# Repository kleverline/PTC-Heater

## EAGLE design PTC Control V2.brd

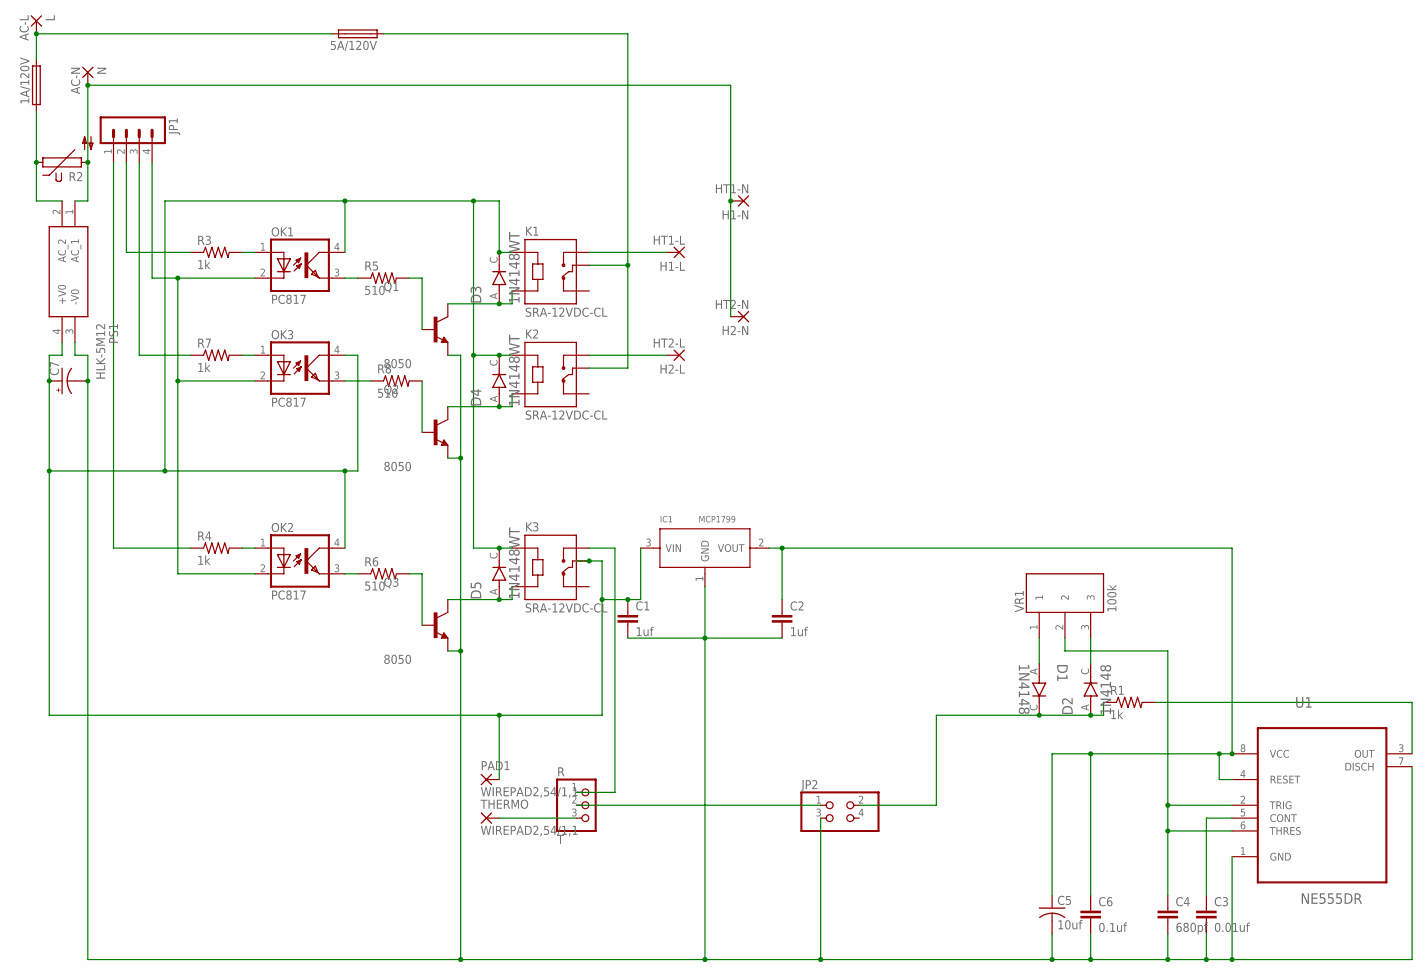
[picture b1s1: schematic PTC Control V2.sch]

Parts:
1A/120V, 5A/120V: SH25
C1, C2: 1uf; C0805
C3: 0.01uf; C0805
C4: 680pf; C0805
C5: 10uf; C1206
C6: 0.1uf; C0805
C7: CPOL-USE3.5-8; E3,5-8
D1, D2: 1N4148; SODFL1608X70N
D3, D4, D5: 1N4148WT; SODFL1608X70N
H1-L: HT1-L; 3,17/1,2
H1-N: HT1-N; 3,17/1,2
H2-L: HT2-L; 3,17/1,2
H2-N: HT2-N; 3,17/1,2
IC1: MCP1799; SOT-23
JP1: MA04-1
JP2: PINHD-2X2; 2X02
K1, K2, K3: SRA-12VDC-CL; RELAY_1-1721150-3
L: AC-L; 3,81/1,4
N: AC-N; 3,81/1,4
OK1, OK2, OK3: PC817; DIL04
PAD1: WIREPAD2,54/1,1; 2,54/1,1
PS1: HLK-5M12; HLK5M12
Q1, Q2, Q3: 8050; TRANS_MMSS8050-H-TP
R: T; 1X03
R1, R3, R4, R7: 1k; R0805
R2: S10K250
R5, R6, R8: 510; R0805
THERMO: WIREPAD2,54/1,1; 2,54/1,1
U1: NE555DR; SOIC127P600X175-8N
VR1: 100k; TRIM_416XA503P

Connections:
GND: C1.2, C2.2, C3.2, C4.2, C5.2, C6.2, C7.-, IC1.1 (GND), JP2.3, PS1.3 (-V0), Q1.2 (E), Q2.2 (E), Q3.2 (E), U1.1 (GND), U1.7 (DISCH)
unnamed: JP2.1, R.2
unnamed: C3.1, U1.5 (CONT)
unnamed: D1.A, VR1.1
unnamed: D2.C, VR1.3
unnamed: 1A/120V.1, PS1.2 (AC_2), R2.1
unnamed: R1.2, U1.3 (OUT)
unnamed: C4.1, U1.2 (TRIG), U1.6 (THRES), VR1.2
unnamed: H1-N.1, H2-N.1, N.1, PS1.1 (AC_1), R2.2
unnamed: OK3.3 (EMIT), R8.1
unnamed: 5A/120V.1, K1.COM, K2.COM
unnamed: OK1.1 (A), R3.2
unnamed: OK2.1 (A), R4.2
unnamed: JP1.4, OK1.2 (C), OK2.2 (C), OK3.2 (C)
unnamed: JP1.1, R4.1
unnamed: JP1.2, R3.1
unnamed: OK1.3 (EMIT), R5.1
unnamed: OK2.3 (EMIT), R6.1
unnamed: Q3.1 (B), R6.2
unnamed: Q2.1 (B), R8.2
unnamed: JP1.3, R7.1
unnamed: D4.A, K2.A2, Q2.3 (C)
unnamed: D5.A, K3.A2, Q3.3 (C)
unnamed: OK3.1 (A), R7.2
unnamed: Q1.1 (B), R5.2
unnamed: H1-L.1, K1.NO
unnamed: D3.A, K1.A2, Q1.3 (C)
unnamed: H2-L.1, K2.NO
unnamed: 1A/120V.2, 5A/120V.2, L.1
unnamed: K3.NO, R.1
unnamed: R.3, THERMO.1
unnamed: C1.1, C7.+, D3.C, D4.C, D5.C, IC1.3 (VIN), K1.A1, K2.A1, K3.A1, K3.COM, OK1.4 (COL), OK2.4 (COL), OK3.4 (COL), PAD1.1, PS1.4 (+V0)
PWM-SIG: D1.C, D2.A, JP2.2, R1.1
VCC-5V: C2.1, C5.1, C6.1, IC1.2 (VOUT), U1.4 (RESET), U1.8 (VCC)

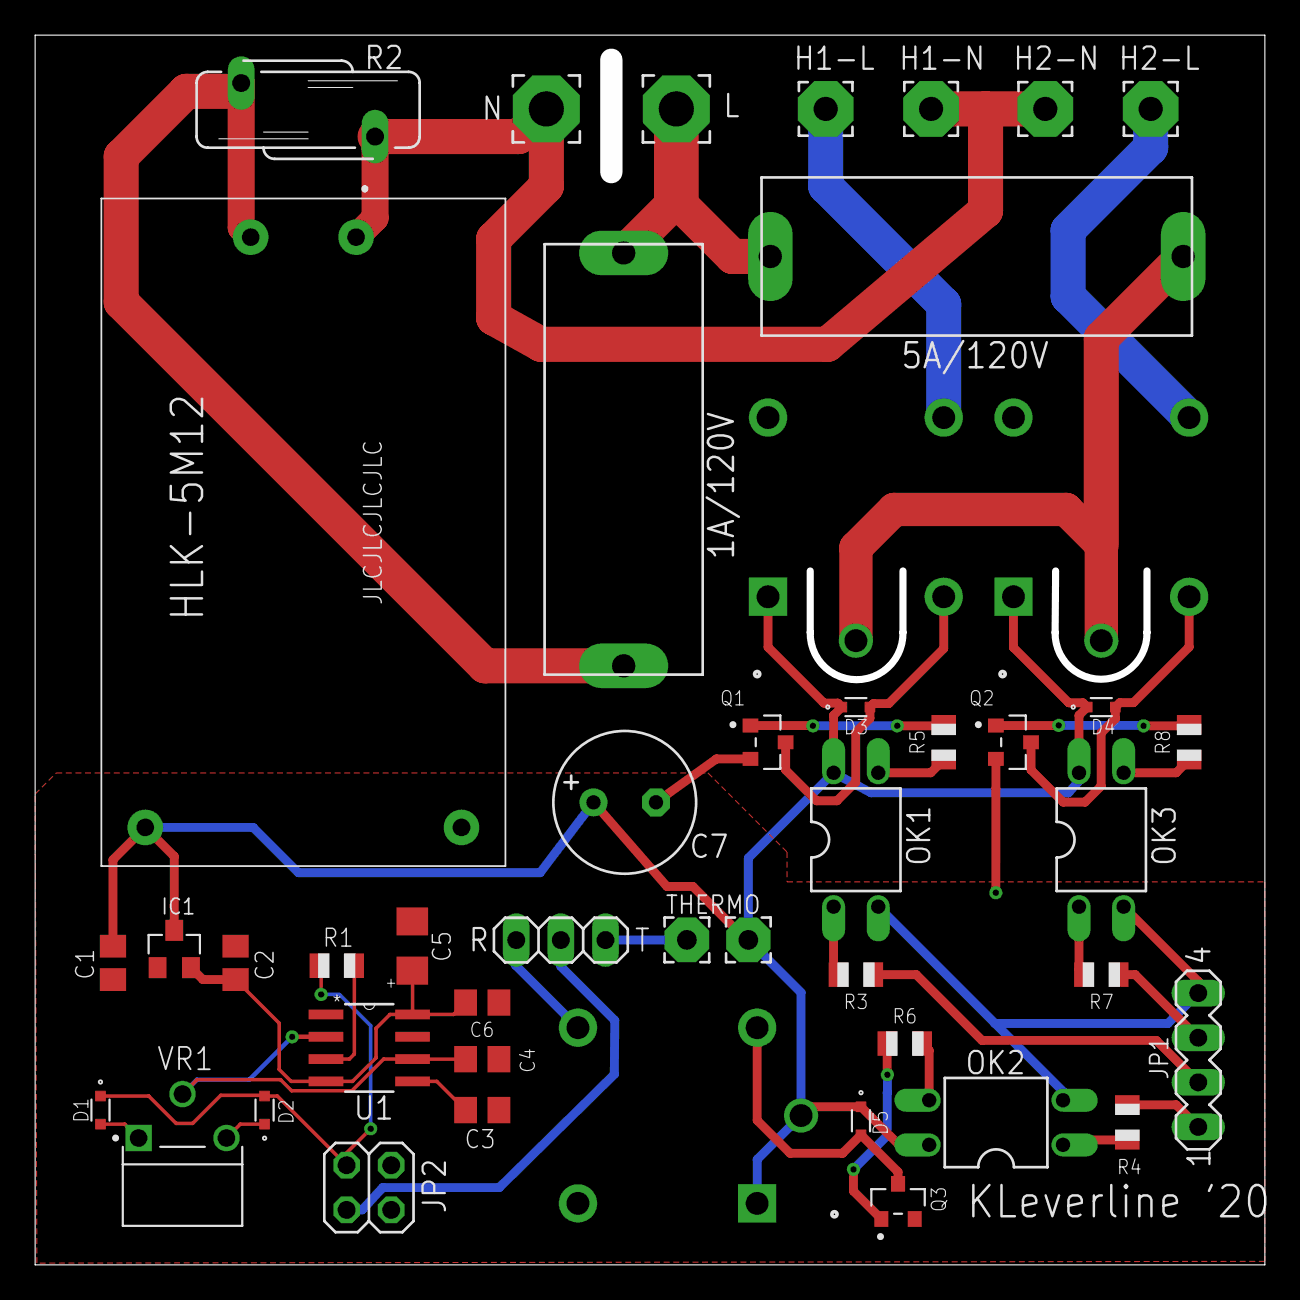
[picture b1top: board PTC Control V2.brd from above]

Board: 2 copper layers, 68.7 x 68.7 mm, 47 parts (1 on the bottom side), 34 nets.

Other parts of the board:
U$1: LOGO-FINAL
